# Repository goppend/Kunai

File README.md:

The Kunai is an open source gamepad based on the Raspberry Pi Pico microcontroller.

Its intended use is either as a standalone controller for Playstation and Playstation 2 systems, or integrated into an all-in-one handheld device that uses the aforementioned systems hardware.

Features
---
- A no-compromises approach to emulating the original functions of the Dualshock 2 gamepad.
- 12 inputs that can be configured as either digital or pressure-sensitive analog buttons.
- 2 rumble motor outputs capable of being driven at 256 pulse-width modulated levels.
- Compatible with readily available aftermarket joysticks. Hall-effect joysticks have yet to be tested, but may be compatible.

Compatibility
---
Not enough testing has been performed to discover any major incompatibilities yet, but as the project evolves, this section will be populated with a list of known good and ill-working titles and applications.

To-do
---
Currently, this project is exiting the "functional prototype" phase, and is not especially useful for gaming, but this will change soon. 
- Shrink the prototype PCB down to work as a drop-in replacement for Dualshock controllers.
- Develop a module as small as possible for rapid integration into custom handheld projects. Version 0 of the module has been released! Check it out in the pcb-module directory.

Attribution
---
[Dangiu/PicoMemcard](https://github.com/dangiu/PicoMemcard/) - Credit for the PIO code responsible for doing gamepad/console communication.

[Loc15/PicoGamepadConverter](https://github.com/Loc15/PicoGamepadConverter/) - Much inspiration for this project, and the multi-core implementation.

[GameSX](https://gamesx.com/controldata/psxcont/psxcont.htm) and [Curious Inventor](https://store.curiousinventor.com/guides/PS2)- Excellent documentation on the protocol and data structures.

Ultipryce - Logo artwork.
___
Disclaimer

This is a passion project by a fan and has no affiliation with Sony or the Playstation brand.

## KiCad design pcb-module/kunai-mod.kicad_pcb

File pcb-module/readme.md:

## Module PCB
This is the Kunai, but in a 22 mm x 22 mm module. The intent is to provide a solution for rapid integration into exiting projects. Thus, most of the I/O is dedicated towards direct connections to discrete buttons, though there's no reason a connection to an ADC couldn't be made just like a full-sized Kunai.

There is KiCad footprint `kunai-mod.kicad_mod` available in the root of this directory, which contains the general pinout compatible with the module.

### Future Development
---
- An integration guide for this module. This document will detail the steps necessary to get as much out of the Kunai as possible for your project.
- HD rumble motors as a potential upgrade via e.g. the DRV2603, which is compatible with LRA as well as traditional ERM rumble motors.

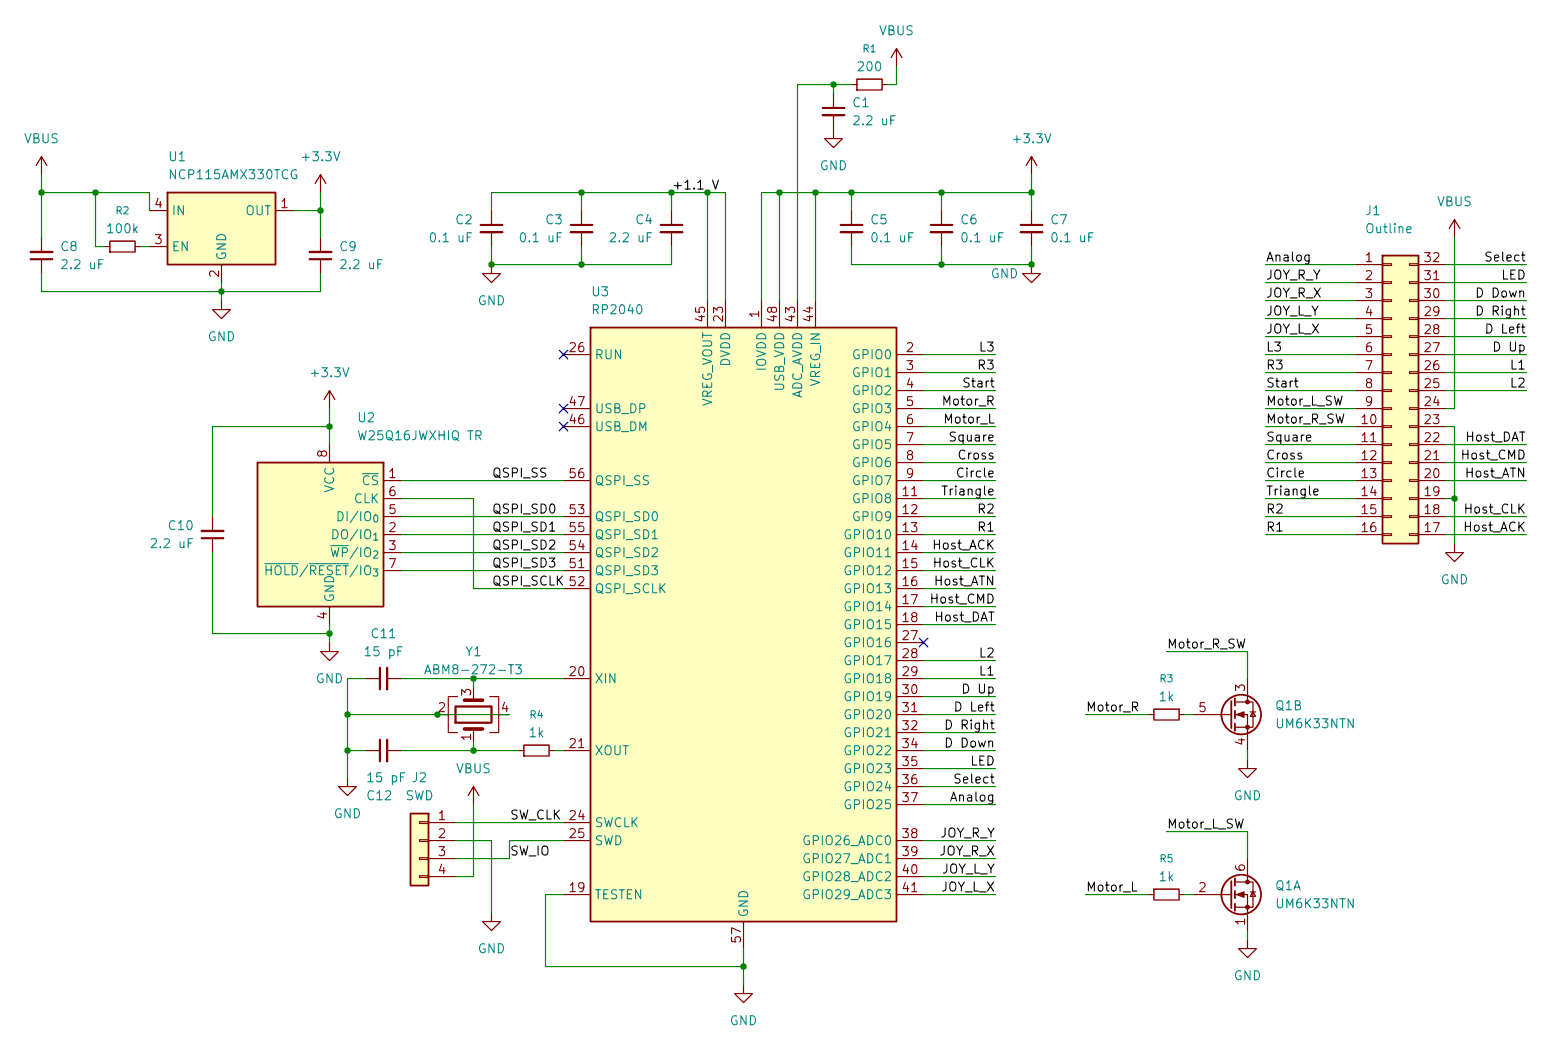
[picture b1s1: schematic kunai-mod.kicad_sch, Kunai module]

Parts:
C1, C4, C8, C9, C10: 2.2 uF; C_0402_1005Metric; part number CC0402KRX5R7BB225; LCSC Part # C170151
C2, C3, C5, C6, C7: 0.1 uF; C_0402_1005Metric; part number C0402C104K4RACTU; LCSC Part # C169842
C11, C12: 15 pF; C_0402_1005Metric; part number CC0402JRNPO8BN150; LCSC Part # C541359
J1: Outline; Kunai-mod-outline; part number N/A; LCSC Part # N/A
J2: SWD; 1x04 1.27mm test point; part number N/A; LCSC Part # N/A
Q1: UM6K33NTN; SOT-363_SC-70-6; part number UM6K33NTN; LCSC Part # C2926471
R1: 200; R_0402_1005Metric; part number RC0402FR-07200RL; LCSC Part # C114764
R2: 100k; R_0402_1005Metric; part number RC0402JR-07100KL; LCSC Part # C106234
R3, R4, R5: 1k; R_0402_1005Metric; part number RC0402JR-071KL; LCSC Part # C105637
U1: NCP115AMX330TCG; XDFN4-JLC; part number NCP115AMX330TCG; LCSC Part # C603503
U2: W25Q16JWXHIQ TR; Winbond_USON-8-1EP_3x2mm_P0.5mm_EP0.2x1.6mm; part number W25Q16JWXHIQ TR; LCSC Part # C2835333
U3: RP2040; QFN-56-1EP_7x7mm_P0.4mm_EP3.2x3.2mm; part number RP2040; LCSC Part # C2040
Y1: ABM8-272-T3; XTAL_ABM8-272-T3; part number ABM8-272-T3; LCSC Part # C20625731

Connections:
+3.3V: C5.1, C6.1, C7.1, C9.2, C10.2, U1.1 (OUT), U2.8 (VCC), U3.1 (IOVDD), U3.10 (IOVDD), U3.22 (IOVDD), U3.33 (IOVDD), U3.42 (IOVDD), U3.44 (VREG_IN), U3.48 (USB_VDD), U3.49 (IOVDD)
/+1.1 V: C2.1, C3.1, C4.1, U3.23 (DVDD), U3.45 (VREG_VOUT), U3.50 (DVDD)
/Analog: J1.1, U3.37 (GPIO25)
/Circle: J1.13, U3.9 (GPIO7)
/Cross: J1.12, U3.8 (GPIO6)
/D Down: J1.30, U3.34 (GPIO22)
/D Left: J1.28, U3.31 (GPIO20)
/D Right: J1.29, U3.32 (GPIO21)
/D Up: J1.27, U3.30 (GPIO19)
/Host_ACK: J1.17, U3.14 (GPIO11)
/Host_ATN: J1.20, U3.16 (GPIO13)
/Host_CLK: J1.18, U3.15 (GPIO12)
/Host_CMD: J1.21, U3.17 (GPIO14)
/Host_DAT: J1.22, U3.18 (GPIO15)
/JOY_L_X: J1.5, U3.41 (GPIO29_ADC3)
/JOY_L_Y: J1.4, U3.40 (GPIO28_ADC2)
/JOY_R_X: J1.3, U3.39 (GPIO27_ADC1)
/JOY_R_Y: J1.2, U3.38 (GPIO26_ADC0)
/L1: J1.26, U3.29 (GPIO18)
/L2: J1.25, U3.28 (GPIO17)
/L3: J1.6, U3.2 (GPIO0)
/LED: J1.31, U3.35 (GPIO23)
/Motor_L: R5.1, U3.6 (GPIO4)
/Motor_L_SW: J1.9, Q1.6 (D)
/Motor_R: R3.2, U3.5 (GPIO3)
/Motor_R_SW: J1.10, Q1.3 (D)
/QSPI_SCLK: U2.6 (CLK), U3.52 (QSPI_SCLK)
/QSPI_SD0: U2.5 (DI/IO_{0}), U3.53 (QSPI_SD0)
/QSPI_SD1: U2.2 (DO/IO_{1}), U3.55 (QSPI_SD1)
/QSPI_SD2: U2.3 (~WP/IO_{2}), U3.54 (QSPI_SD2)
/QSPI_SD3: U2.7 (~HOLD/~RESET/IO_{3}), U3.51 (QSPI_SD3)
/QSPI_SS: U2.1 (~CS), U3.56 (QSPI_SS)
/R1: J1.16, U3.13 (GPIO10)
/R2: J1.15, U3.12 (GPIO9)
/R3: J1.7, U3.3 (GPIO1)
/SW_CLK: J2.1, U3.24 (SWCLK)
/SW_IO: J2.3, U3.25 (SWD)
/Select: J1.32, U3.36 (GPIO24)
/Square: J1.11, U3.7 (GPIO5)
/Start: J1.8, U3.4 (GPIO2)
/Triangle: J1.14, U3.11 (GPIO8)
GND: C1.2, C2.2, C3.2, C4.2, C5.2, C6.2, C7.2, C8.1, C9.1, C10.1, C11.1, C12.1, J1.19, J1.23, J2.2, Q1.1 (S), Q1.4 (S), U1.2 (GND), U1.5 (GND), U2.4 (GND), U3.19 (TESTEN), U3.57 (GND), Y1.2, Y1.4
unnamed: C12.2, R4.1, Y1.1
unnamed: Q1.2 (G), R5.2
unnamed: Q1.5 (G), R3.1
unnamed: R2.2, U1.3 (EN)
unnamed: C1.1, R1.1, U3.43 (ADC_AVDD)
unnamed: C11.2, U3.20 (XIN), Y1.3
unnamed: R4.2, U3.21 (XOUT)
VBUS: C8.2, J1.24, J2.4, R1.2, R2.1, U1.4 (IN)

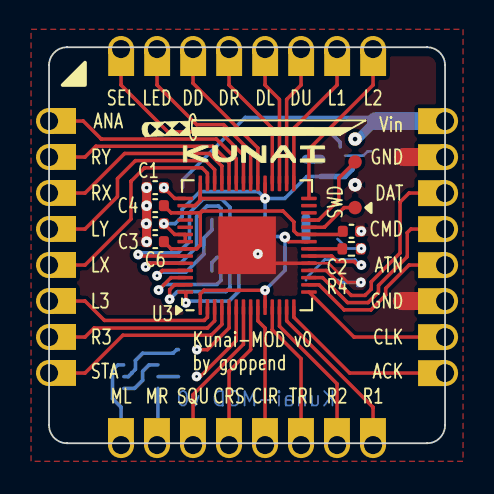
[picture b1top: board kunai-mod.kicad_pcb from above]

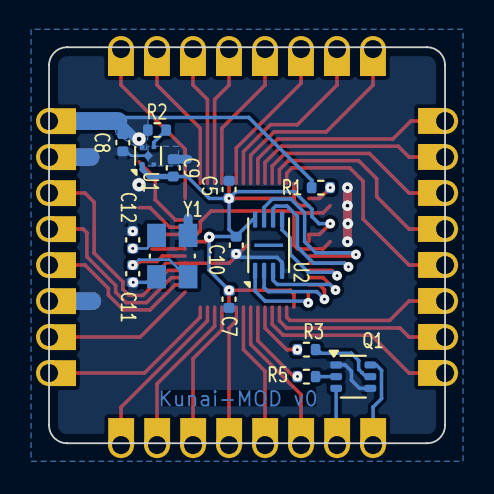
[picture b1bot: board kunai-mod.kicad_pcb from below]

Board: 2 copper layers, 22.0 x 22.0 mm, 24 parts (15 on the bottom side), 50 nets.

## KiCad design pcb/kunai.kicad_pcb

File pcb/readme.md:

## Prototype PCB
This is the first release of the Kunai PCB. It's a functional prototype, and as such isn't recommended for gaming yet.

A few things to keep in mind, for anyone interested in building one:
- I have no enclosure designed yet, but the general button layout is 1:1 with an original Dualshock 2.
- The rectangular connectors were for testing, to easily swap a pressure sensor from one spot to another. I would not recommend using these connectors and instead replace the footprint with a normal soldered footprint since that portion of the testing is complete.

### Future Development
---
- Replace aftermarket PS2 joysticks with PS4 since hall effect versions with that footprint exist.
- Replace the Pico with a RP2040.

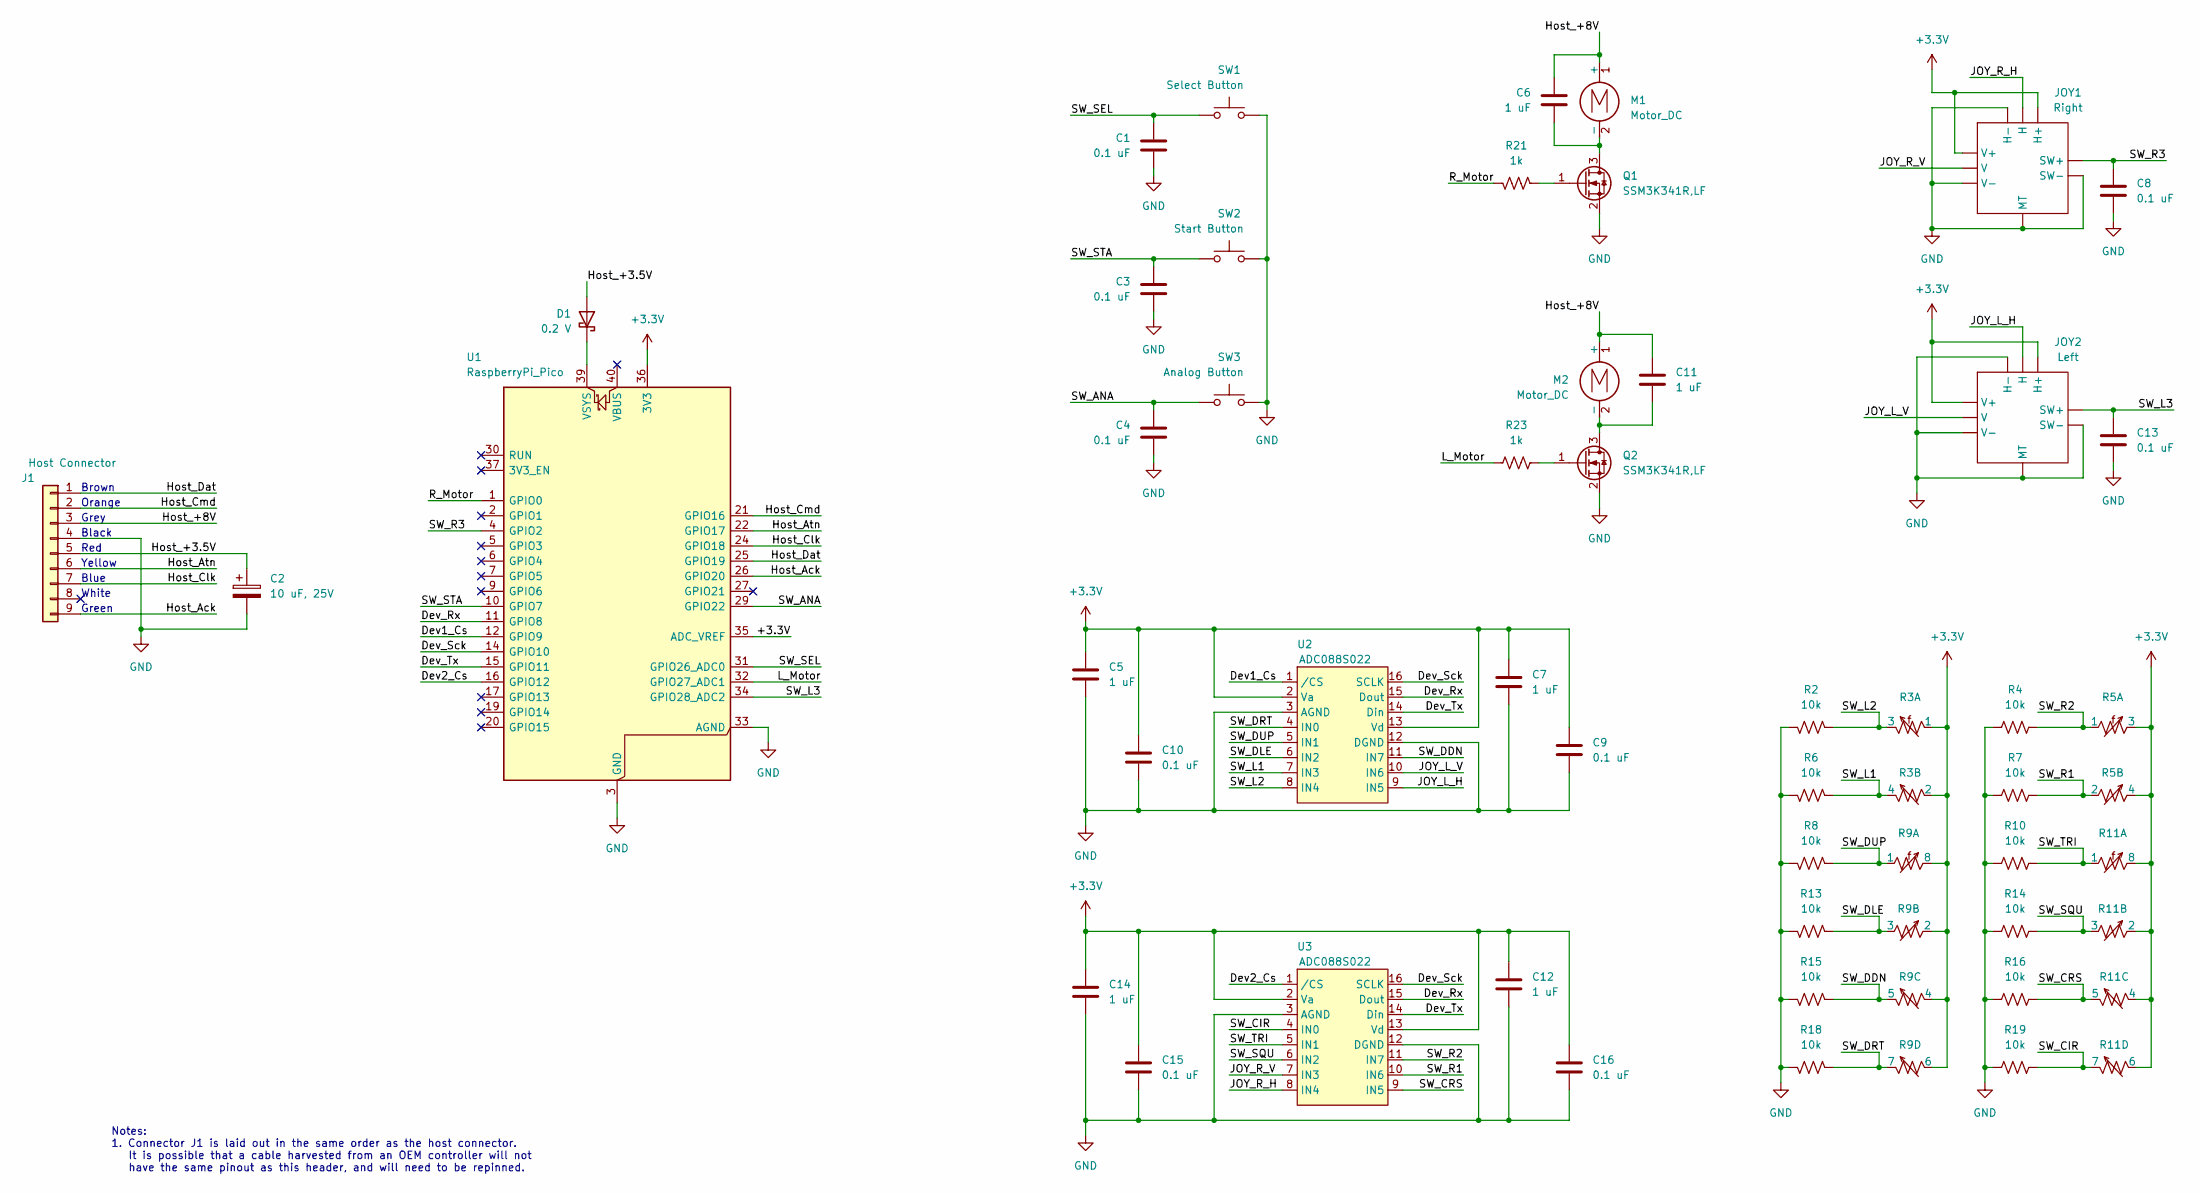
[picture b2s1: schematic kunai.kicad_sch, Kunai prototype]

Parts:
C1, C3, C4, C8, C9, C10, C13, C15, C16: 0.1 uF; C_0805_2012Metric_Pad1.18x1.45mm_HandSolder; Part Number C0805C104K5RAC7210
C2: 10 uF, 25V; Panasonic ECE-A1EKA100; Part Number ECE-A1EKA100
C5, C7, C12, C14: 1 uF; C_0805_2012Metric_Pad1.18x1.45mm_HandSolder; Part Number C0805C105K3RACTU
C6, C11: 1 uF; C_0805_2012Metric_Pad1.18x1.45mm_HandSolder; Part Number GRJ21BC72A105KE11L
D1: 0.2 V; Nexperia_CFP3_SOD-123W; Part Number MBR120VLSFT1G
J1: Host Connector; PinHeader_1x09_P2.00mm_Vertical; Part Number N/A
JOY1: Right; PS4_joystick; Part Number N/A
JOY2: Left; PS4_joystick; Part Number N/A
M1, M2: Motor_DC; PinHeader_2x01_P2.54mm_Vertical_SMD; Part Number N/A
Q1, Q2: SSM3K341R,LF; SOT-23_Handsoldering; Part Number SSM3K341R,LF
R2, R4, R6, R7, R8, R10, R13, R14, R15, R16, R18, R19: 10k; R_0805_2012Metric_Pad1.20x1.40mm_HandSolder; Part Number RN73R2ATTD1002B25
R3, R5: BCS-102-L-D-HE; Samtec BCS Series; Part Number BCS-102-L-D-HE
R9, R11: HLE-104-02-F-DV-BE; Samtec HLE Series, through board; Part Number HLE-104-02-F-DV-BE
R21, R23: 1k; R_0805_2012Metric_Pad1.20x1.40mm_HandSolder; Part Number CRCW08051K00FKEA
SW1: Select Button; E-Switch TL3301 Series switch; Part Number TL3301SPF160QG
SW2: Start Button; E-Switch TL3301 Series switch; Part Number TL3301SPF160QG
SW3: Analog Button; SW_SPST_Omron_B3FS-100xP; Part Number B3FS-1000
U1: RaspberryPi_Pico; Raspberry Pi Pico Reduced Pin Footprint; Part Number SC0915
U2, U3: ADC088S022; TSSOP-16_4.4x5mm_P0.65mm; Part Number ADC088S022CIMTX/NOPB

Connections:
+3.3V: C5.1, C7.1, C9.1, C10.1, C12.1, C14.1, C15.1, C16.1, JOY1.H1 (H+), JOY1.V1 (V+), JOY2.H1 (H+), JOY2.V1 (V+), R3.1, R3.2, R5.3, R5.4, R9.2, R9.4, R9.6, R9.8, R11.2, R11.4, R11.6, R11.8, U1.35 (ADC_VREF), U1.36 (3V3), U2.2 (Va), U2.13 (Vd), U3.2 (Va), U3.13 (Vd)
/Dev1_Cs: U1.12 (GPIO9), U2.1 (/CS)
/Dev2_Cs: U1.16 (GPIO12), U3.1 (/CS)
/Dev_Rx: U1.11 (GPIO8), U2.15 (Dout), U3.15 (Dout)
/Dev_Sck: U1.14 (GPIO10), U2.16 (SCLK), U3.16 (SCLK)
/Dev_Tx: U1.15 (GPIO11), U2.14 (Din), U3.14 (Din)
/Host_+3.5V: C2.1, D1.2 (A), J1.5
/Host_+8V: C6.1, C11.1, J1.3, M1.1 (+), M2.1 (+)
/Host_Ack: J1.9, U1.26 (GPIO20)
/Host_Atn: J1.6, U1.22 (GPIO17)
/Host_Clk: J1.7, U1.24 (GPIO18)
/Host_Cmd: J1.2, U1.21 (GPIO16)
/Host_Dat: J1.1, U1.25 (GPIO19)
/JOY_L_H: JOY2.H2 (H), U2.9 (IN5)
/JOY_L_V: JOY2.V2 (V), U2.10 (IN6)
/JOY_R_H: JOY1.H2 (H), U3.8 (IN4)
/JOY_R_V: JOY1.V2 (V), U3.7 (IN3)
/L_Motor: R23.1, U1.32 (GPIO27_ADC1)
/R_Motor: R21.2, U1.1 (GPIO0)
/SW_ANA: C4.1, SW3.1, U1.29 (GPIO22)
/SW_CIR: R11.7, R19.2, U3.4 (IN0)
/SW_CRS: R11.5, R16.2, U3.9 (IN5)
/SW_DDN: R9.5, R15.1, U2.11 (IN7)
/SW_DLE: R9.3, R13.1, U2.6 (IN2)
/SW_DRT: R9.7, R18.1, U2.4 (IN0)
/SW_DUP: R8.1, R9.1, U2.5 (IN1)
/SW_L1: R3.4, R6.1, U2.7 (IN3)
/SW_L2: R2.1, R3.3, U2.8 (IN4)
/SW_L3: C13.1, JOY2.S1 (SW+), U1.34 (GPIO28_ADC2)
/SW_R1: R5.2, R7.2, U3.10 (IN6)
/SW_R2: R4.2, R5.1, U3.11 (IN7)
/SW_R3: C8.1, JOY1.S1 (SW+), U1.4 (GPIO2)
/SW_SEL: C1.1, SW1.2, U1.31 (GPIO26_ADC0)
/SW_SQU: R11.3, R14.2, U3.6 (IN2)
/SW_STA: C3.1, SW2.2, U1.10 (GPIO7)
/SW_TRI: R10.2, R11.1, U3.5 (IN1)
GND: C1.2, C2.2, C3.2, C4.2, C5.2, C7.2, C8.2, C9.2, C10.2, C12.2, C13.2, C14.2, C15.2, C16.2, J1.4, JOY1.H3 (H-), JOY1.MT, JOY1.S2 (SW-), JOY1.V3 (V-), JOY2.H3 (H-), JOY2.MT, JOY2.S2 (SW-), JOY2.V3 (V-), Q1.2 (S), Q2.2 (S), R2.2, R4.1, R6.2, R7.1, R8.2, R10.1, R13.2, R14.1, R15.2, R16.1, R18.2, R19.1, SW1.1, SW2.1, SW3.2, U1.3 (GND), U1.8 (GND), U1.13 (GND), U1.18 (GND), U1.23 (GND), U1.28 (GND), U1.33 (AGND), U1.38 (GND), U2.3 (AGND), U2.12 (DGND), U3.3 (AGND), U3.12 (DGND)
unnamed: D1.1 (K), U1.39 (VSYS)
unnamed: C6.2, M1.2 (-), Q1.3 (D)
unnamed: C11.2, M2.2 (-), Q2.3 (D)
unnamed: Q1.1 (G), R21.1
unnamed: Q2.1 (G), R23.2

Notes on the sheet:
Red
Yellow
White
Blue
Grey
Orange
Brown
Green
Black
Notes: 1. Connector J1 is laid out in the same order as the host connector. It is possible that a cable harvested from an OEM controller will not have the same pinout as this header, and will need to be repinned.

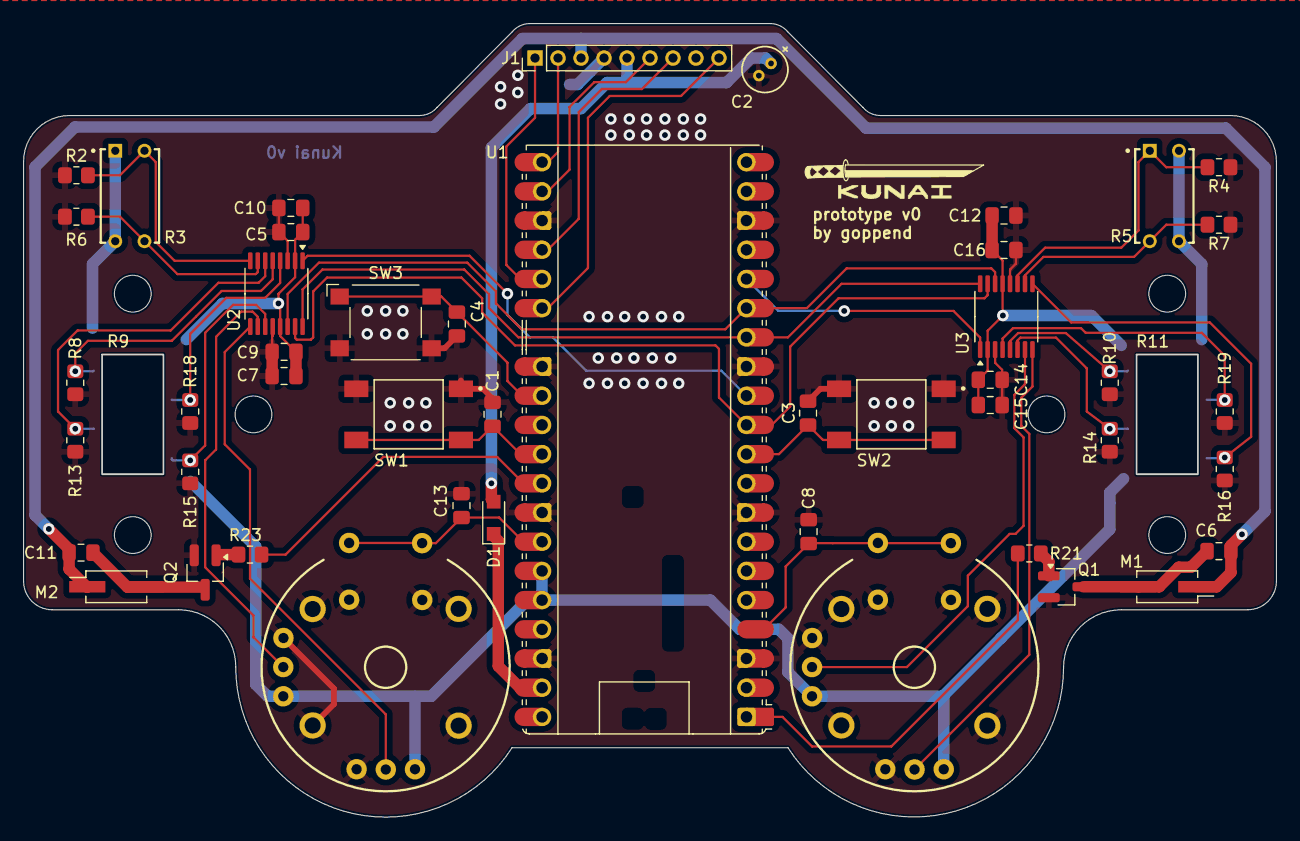
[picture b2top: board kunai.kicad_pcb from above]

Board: 2 copper layers, 109.0 x 69.0 mm, 48 parts (0 on the bottom side), 42 nets.

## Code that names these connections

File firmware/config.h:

// define pin connections
#define GPIO_L3         0
#define GPIO_R3         1
#define GPIO_START      2
#define GPIO_L_MOTOR    3
#define GPIO_R_MOTOR    4
#define GPIO_LED        23
#define GPIO_SELECT     24
#define GPIO_ANALOG     25

#ifdef DIGITAL_INPUTS
    // define digital inputs
    #define GPIO_FACE_SQUARE    5
    #define GPIO_FACE_CROSS     6
    #define GPIO_FACE_CIRCLE    7
    #define GPIO_FACE_TRIANGLE  8
    #define GPIO_SHOULDER_R2    9
    #define GPIO_SHOULDER_R1    10
    #define GPIO_SHOULDER_L2    17
    #define GPIO_SHOULDER_L1    18
    #define GPIO_DPAD_UP        19
    #define GPIO_DPAD_LEFT      20
    #define GPIO_DPAD_RIGHT     21
    #define GPIO_DPAD_DOWN      22
    #define GPIO_ANA_R_Y        26
    #define GPIO_ANA_R_X        27
    #define GPIO_ANA_L_Y        28
    #define GPIO_ANA_L_X        29
#else
    // define pins for external ADCs
    #define GPIO_LEFT_ADC   9 // adc 1
    #define GPIO_RIGHT_ADC  12 // adc 2
    #define SPI_DEV_RX      8
    #define SPI_DEV_SCK     10
    #define SPI_DEV_TX      11
#endif

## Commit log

2025-10-12 First commit, v0 hardware and firmware
2025-10-12 Fix readmes not showing images
2025-10-25 Add module PCB
2025-10-25 Add footprint and update readme, small tweaks to pcb/schematic.
2025-10-25 Update main readme
2025-10-26 Add prototype firmware support for module.
2026-03-08 Update firmware, cleaned up for module, remove prototype stuff.
